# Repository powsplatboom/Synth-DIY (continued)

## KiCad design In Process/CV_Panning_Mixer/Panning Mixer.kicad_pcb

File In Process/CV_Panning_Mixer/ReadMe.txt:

Replacement design for the stereo mixer I built previously. 
Works relatively well, but panning circuit need reworked to achieve constant power panning. Distortion gain needs adjusted to achieve more constant volume.
Likely to switch to the SSI2164 with the redesign to save on cost and board size. The AS3360 is a finnicky chip that requires too many external components to function.
Will also be adding expandability to the board so that a microphone pre-amp can be added as a separate upgrade.
Would also like to add mute switches to all channels.

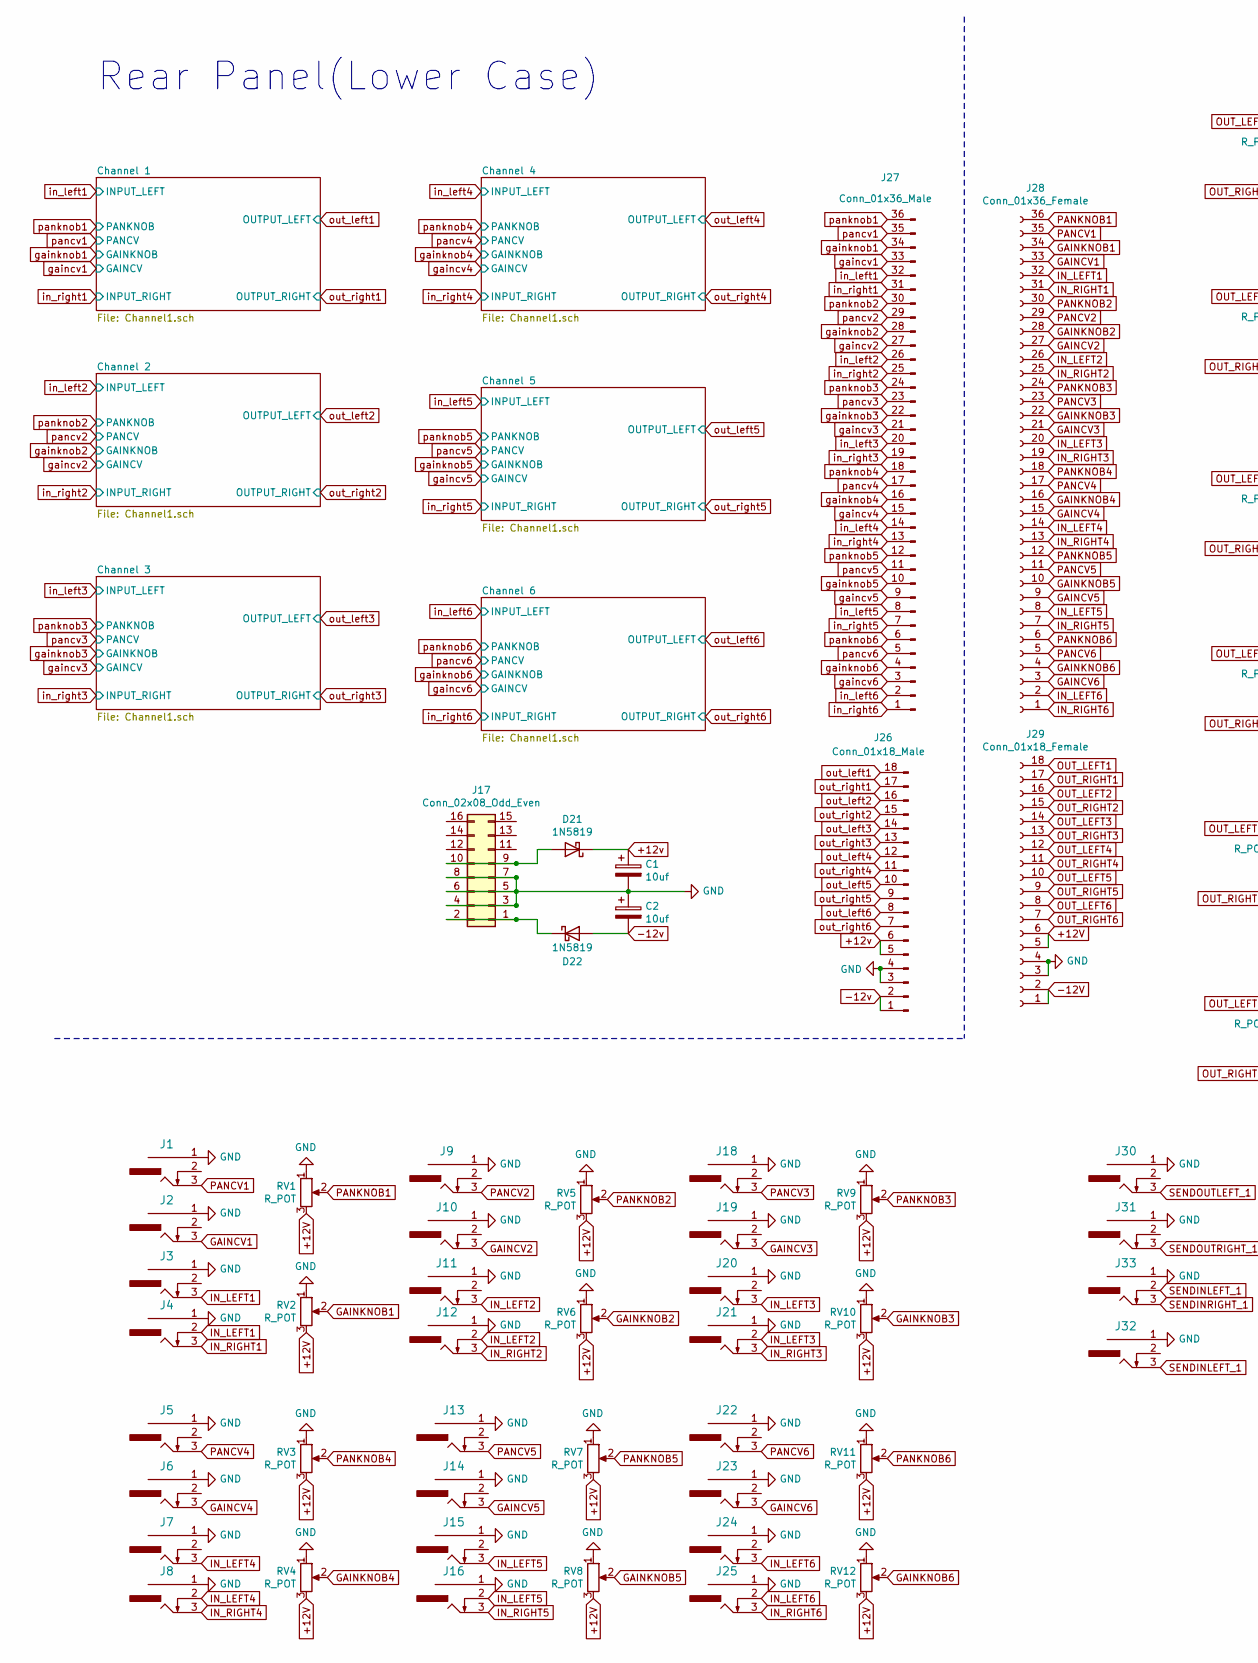
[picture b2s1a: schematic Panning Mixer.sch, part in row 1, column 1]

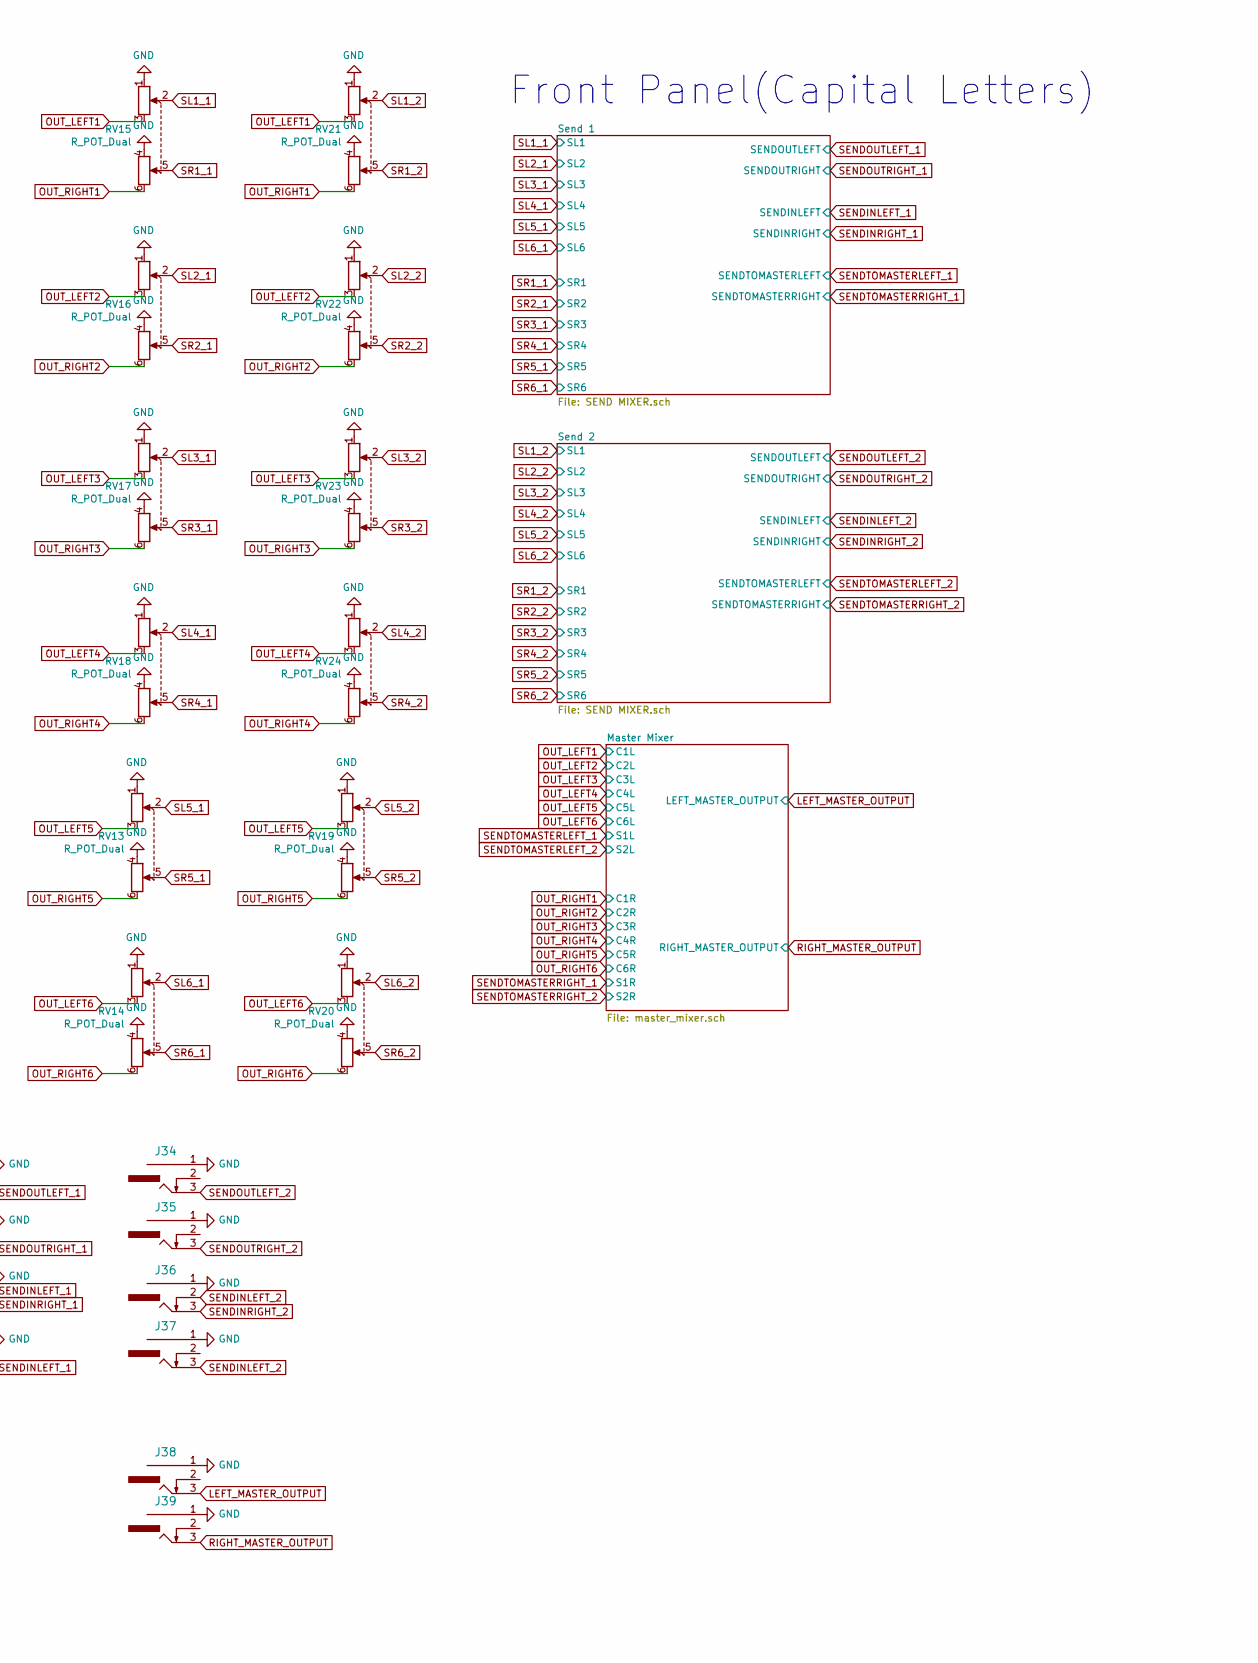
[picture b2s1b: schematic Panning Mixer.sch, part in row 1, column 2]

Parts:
C1, C2: 10uf; CP_Elec_5x5.4
D21, D22: 1N5819; D_DO-41_SOD81_P10.16mm_Horizontal
J1, J2, J3, J4, J5, J6, J7, J8, J9, J10, J11, J12, J13, J14, J15, J16, J18, J19, J20, J21, J22, J23, J24, J25, J30, J31, J32, J33, J34, J35, J36, J37, J38, J39: PJ301_THONKICONN1; PJ-3001_Mono_Phone
J17: Conn_02x08_Odd_Even; IDC-Header_2x08_P2.54mm_Vertical
J26: Conn_01x18_Male; PinHeader_1x18_P2.54mm_Vertical
J27: Conn_01x36_Male; PinHeader_1x36_P2.54mm_Vertical
J28: Conn_01x36_Female; PinSocket_1x36_P2.54mm_Vertical
J29: Conn_01x18_Female; PinSocket_1x18_P2.54mm_Vertical
RV1, RV2, RV3, RV4, RV5, RV6, RV7, RV8, RV9, RV10, RV11, RV12: R_POT; Potentiometer_Alpha_RD901F-40-00D_Single_Vertical
RV13, RV14, RV15, RV16, RV17, RV18, RV19, RV20, RV21, RV22, RV23, RV24: R_POT_Dual; Potentiometer_Alpha_RD902F-40-00D_Dual_Vertical

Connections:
+12V: J29.5, J29.6, RV1.3, RV2.3, RV3.3, RV4.3, RV5.3, RV6.3, RV7.3, RV8.3, RV9.3, RV10.3, RV11.3, RV12.3; also elsewhere on the board
+12v: C1.1, D21.1 (K), J26.5, J26.6; also elsewhere on the board
-12V: J29.1, J29.2; also elsewhere on the board
-12v: C2.2, D22.2 (A), J26.1, J26.2; also elsewhere on the board
GAINCV1: J2.3, J28.33
GAINCV2: J10.3, J28.27
GAINCV3: J19.3, J28.21
GAINCV4: J6.3, J28.15
GAINCV5: J14.3, J28.9
GAINCV6: J23.3, J28.3
GAINKNOB1: J28.34, RV2.2
GAINKNOB2: J28.28, RV6.2
GAINKNOB3: J28.22, RV10.2
GAINKNOB4: J28.16, RV4.2
GAINKNOB5: J28.10, RV8.2
GAINKNOB6: J28.4, RV12.2
GND: C1.2, C2.1, J1.1, J2.1, J3.1, J4.1, J5.1, J6.1, J7.1, J8.1, J9.1, J10.1, J11.1, J12.1, J13.1, J14.1, J15.1, J16.1, J17.3, J17.4, J17.5, J17.6, J17.7, J17.8, J18.1, J19.1, J20.1, J21.1, J22.1, J23.1, J24.1, J25.1, J26.3, J26.4, J29.3, J29.4, J30.1, J31.1, J32.1, J33.1, J34.1, J35.1, J36.1, J37.1, J38.1, J39.1, RV1.1, RV2.1, RV3.1, RV4.1, RV5.1, RV6.1, RV7.1, RV8.1, RV9.1, RV10.1, RV11.1, RV12.1, RV13.1, RV13.4, RV14.1, RV14.4, RV15.1, RV15.4, RV16.1, RV16.4, RV17.1, RV17.4, RV18.1, RV18.4, RV19.1, RV19.4, RV20.1, RV20.4, RV21.1, RV21.4, RV22.1, RV22.4, RV23.1, RV23.4, RV24.1, RV24.4; also elsewhere on the board
IN_LEFT1: J3.3, J4.2, J28.32
IN_LEFT2: J11.3, J12.2, J28.26
IN_LEFT3: J20.3, J21.2, J28.20
IN_LEFT4: J7.3, J8.2, J28.14
IN_LEFT5: J15.3, J16.2, J28.8
IN_LEFT6: J24.3, J25.2, J28.2
IN_RIGHT1: J4.3, J28.31
IN_RIGHT2: J12.3, J28.25
IN_RIGHT3: J21.3, J28.19
IN_RIGHT4: J8.3, J28.13
IN_RIGHT5: J16.3, J28.7
IN_RIGHT6: J25.3, J28.1
LEFT_MASTER_OUTPUT: J38.3; also elsewhere on the board
unnamed: D21.2 (A), J17.9, J17.10
unnamed: D22.1 (K), J17.1, J17.2
OUT_LEFT1: J29.18, RV15.3, RV21.3; also elsewhere on the board
OUT_LEFT2: J29.16, RV16.3, RV22.3; also elsewhere on the board
OUT_LEFT3: J29.14, RV17.3, RV23.3; also elsewhere on the board
OUT_LEFT4: J29.12, RV18.3, RV24.3; also elsewhere on the board
OUT_LEFT5: J29.10, RV13.3, RV19.3; also elsewhere on the board
OUT_LEFT6: J29.8, RV14.3, RV20.3; also elsewhere on the board
OUT_RIGHT1: J29.17, RV15.6, RV21.6; also elsewhere on the board
OUT_RIGHT2: J29.15, RV16.6, RV22.6; also elsewhere on the board
OUT_RIGHT3: J29.13, RV17.6, RV23.6; also elsewhere on the board
OUT_RIGHT4: J29.11, RV18.6, RV24.6; also elsewhere on the board
OUT_RIGHT5: J29.9, RV13.6, RV19.6; also elsewhere on the board
OUT_RIGHT6: J29.7, RV14.6, RV20.6; also elsewhere on the board
PANCV1: J1.3, J28.35
PANCV2: J9.3, J28.29
PANCV3: J18.3, J28.23
PANCV4: J5.3, J28.17
PANCV5: J13.3, J28.11
PANCV6: J22.3, J28.5
PANKNOB1: J28.36, RV1.2
PANKNOB2: J28.30, RV5.2
PANKNOB3: J28.24, RV9.2
PANKNOB4: J28.18, RV3.2
PANKNOB5: J28.12, RV7.2
PANKNOB6: J28.6, RV11.2
RIGHT_MASTER_OUTPUT: J39.3; also elsewhere on the board
SENDINRIGHT_1: J33.3; also elsewhere on the board
SENDINRIGHT_2: J36.3; also elsewhere on the board
SENDOUTLEFT_1: J30.3; also elsewhere on the board
SENDOUTLEFT_2: J34.3; also elsewhere on the board
SENDOUTRIGHT_1: J31.3; also elsewhere on the board
SENDOUTRIGHT_2: J35.3; also elsewhere on the board
SL1_1: RV15.2; also elsewhere on the board
SL1_2: RV21.2; also elsewhere on the board
SL2_1: RV16.2; also elsewhere on the board
SL2_2: RV22.2; also elsewhere on the board
SL3_1: RV17.2; also elsewhere on the board
SL3_2: RV23.2; also elsewhere on the board
SL4_1: RV18.2; also elsewhere on the board
SL4_2: RV24.2; also elsewhere on the board
SL5_1: RV13.2; also elsewhere on the board
SL5_2: RV19.2; also elsewhere on the board
SL6_1: RV14.2; also elsewhere on the board
SL6_2: RV20.2; also elsewhere on the board
SR1_1: RV15.5; also elsewhere on the board
SR1_2: RV21.5; also elsewhere on the board
SR2_1: RV16.5; also elsewhere on the board
SR2_2: RV22.5; also elsewhere on the board
SR3_1: RV17.5; also elsewhere on the board
SR3_2: RV23.5; also elsewhere on the board
SR4_1: RV18.5; also elsewhere on the board
SR4_2: RV24.5; also elsewhere on the board
SR5_1: RV13.5; also elsewhere on the board
SR5_2: RV19.5; also elsewhere on the board
SR6_1: RV14.5; also elsewhere on the board
SR6_2: RV20.5; also elsewhere on the board
gaincv1: J27.33; also elsewhere on the board
gaincv2: J27.27; also elsewhere on the board
gaincv3: J27.21; also elsewhere on the board
gaincv4: J27.15; also elsewhere on the board
gaincv5: J27.9; also elsewhere on the board
gaincv6: J27.3; also elsewhere on the board
gainknob1: J27.34; also elsewhere on the board
gainknob2: J27.28; also elsewhere on the board
gainknob3: J27.22; also elsewhere on the board
gainknob4: J27.16; also elsewhere on the board
gainknob5: J27.10; also elsewhere on the board
gainknob6: J27.4; also elsewhere on the board
in_left1: J27.32; also elsewhere on the board
in_left2: J27.26; also elsewhere on the board
in_left3: J27.20; also elsewhere on the board
in_left4: J27.14; also elsewhere on the board
in_left5: J27.8; also elsewhere on the board
in_left6: J27.2; also elsewhere on the board
in_right1: J27.31; also elsewhere on the board
in_right2: J27.25; also elsewhere on the board
in_right3: J27.19; also elsewhere on the board
in_right4: J27.13; also elsewhere on the board
in_right5: J27.7; also elsewhere on the board
in_right6: J27.1; also elsewhere on the board
out_left1: J26.18; also elsewhere on the board
out_left2: J26.16; also elsewhere on the board
out_left3: J26.14; also elsewhere on the board
out_left4: J26.12; also elsewhere on the board
out_left5: J26.10; also elsewhere on the board
out_left6: J26.8; also elsewhere on the board
out_right1: J26.17; also elsewhere on the board
out_right2: J26.15; also elsewhere on the board
out_right3: J26.13; also elsewhere on the board
out_right4: J26.11; also elsewhere on the board
out_right5: J26.9; also elsewhere on the board
out_right6: J26.7; also elsewhere on the board
pancv1: J27.35; also elsewhere on the board
pancv2: J27.29; also elsewhere on the board
pancv3: J27.23; also elsewhere on the board
pancv4: J27.17; also elsewhere on the board
pancv5: J27.11; also elsewhere on the board
pancv6: J27.5; also elsewhere on the board
panknob1: J27.36; also elsewhere on the board
panknob2: J27.30; also elsewhere on the board
panknob3: J27.24; also elsewhere on the board
panknob4: J27.18; also elsewhere on the board
panknob5: J27.12; also elsewhere on the board
panknob6: J27.6; also elsewhere on the board

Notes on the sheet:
Front Panel(Capital Letters)
Rear Panel(Lower Case)

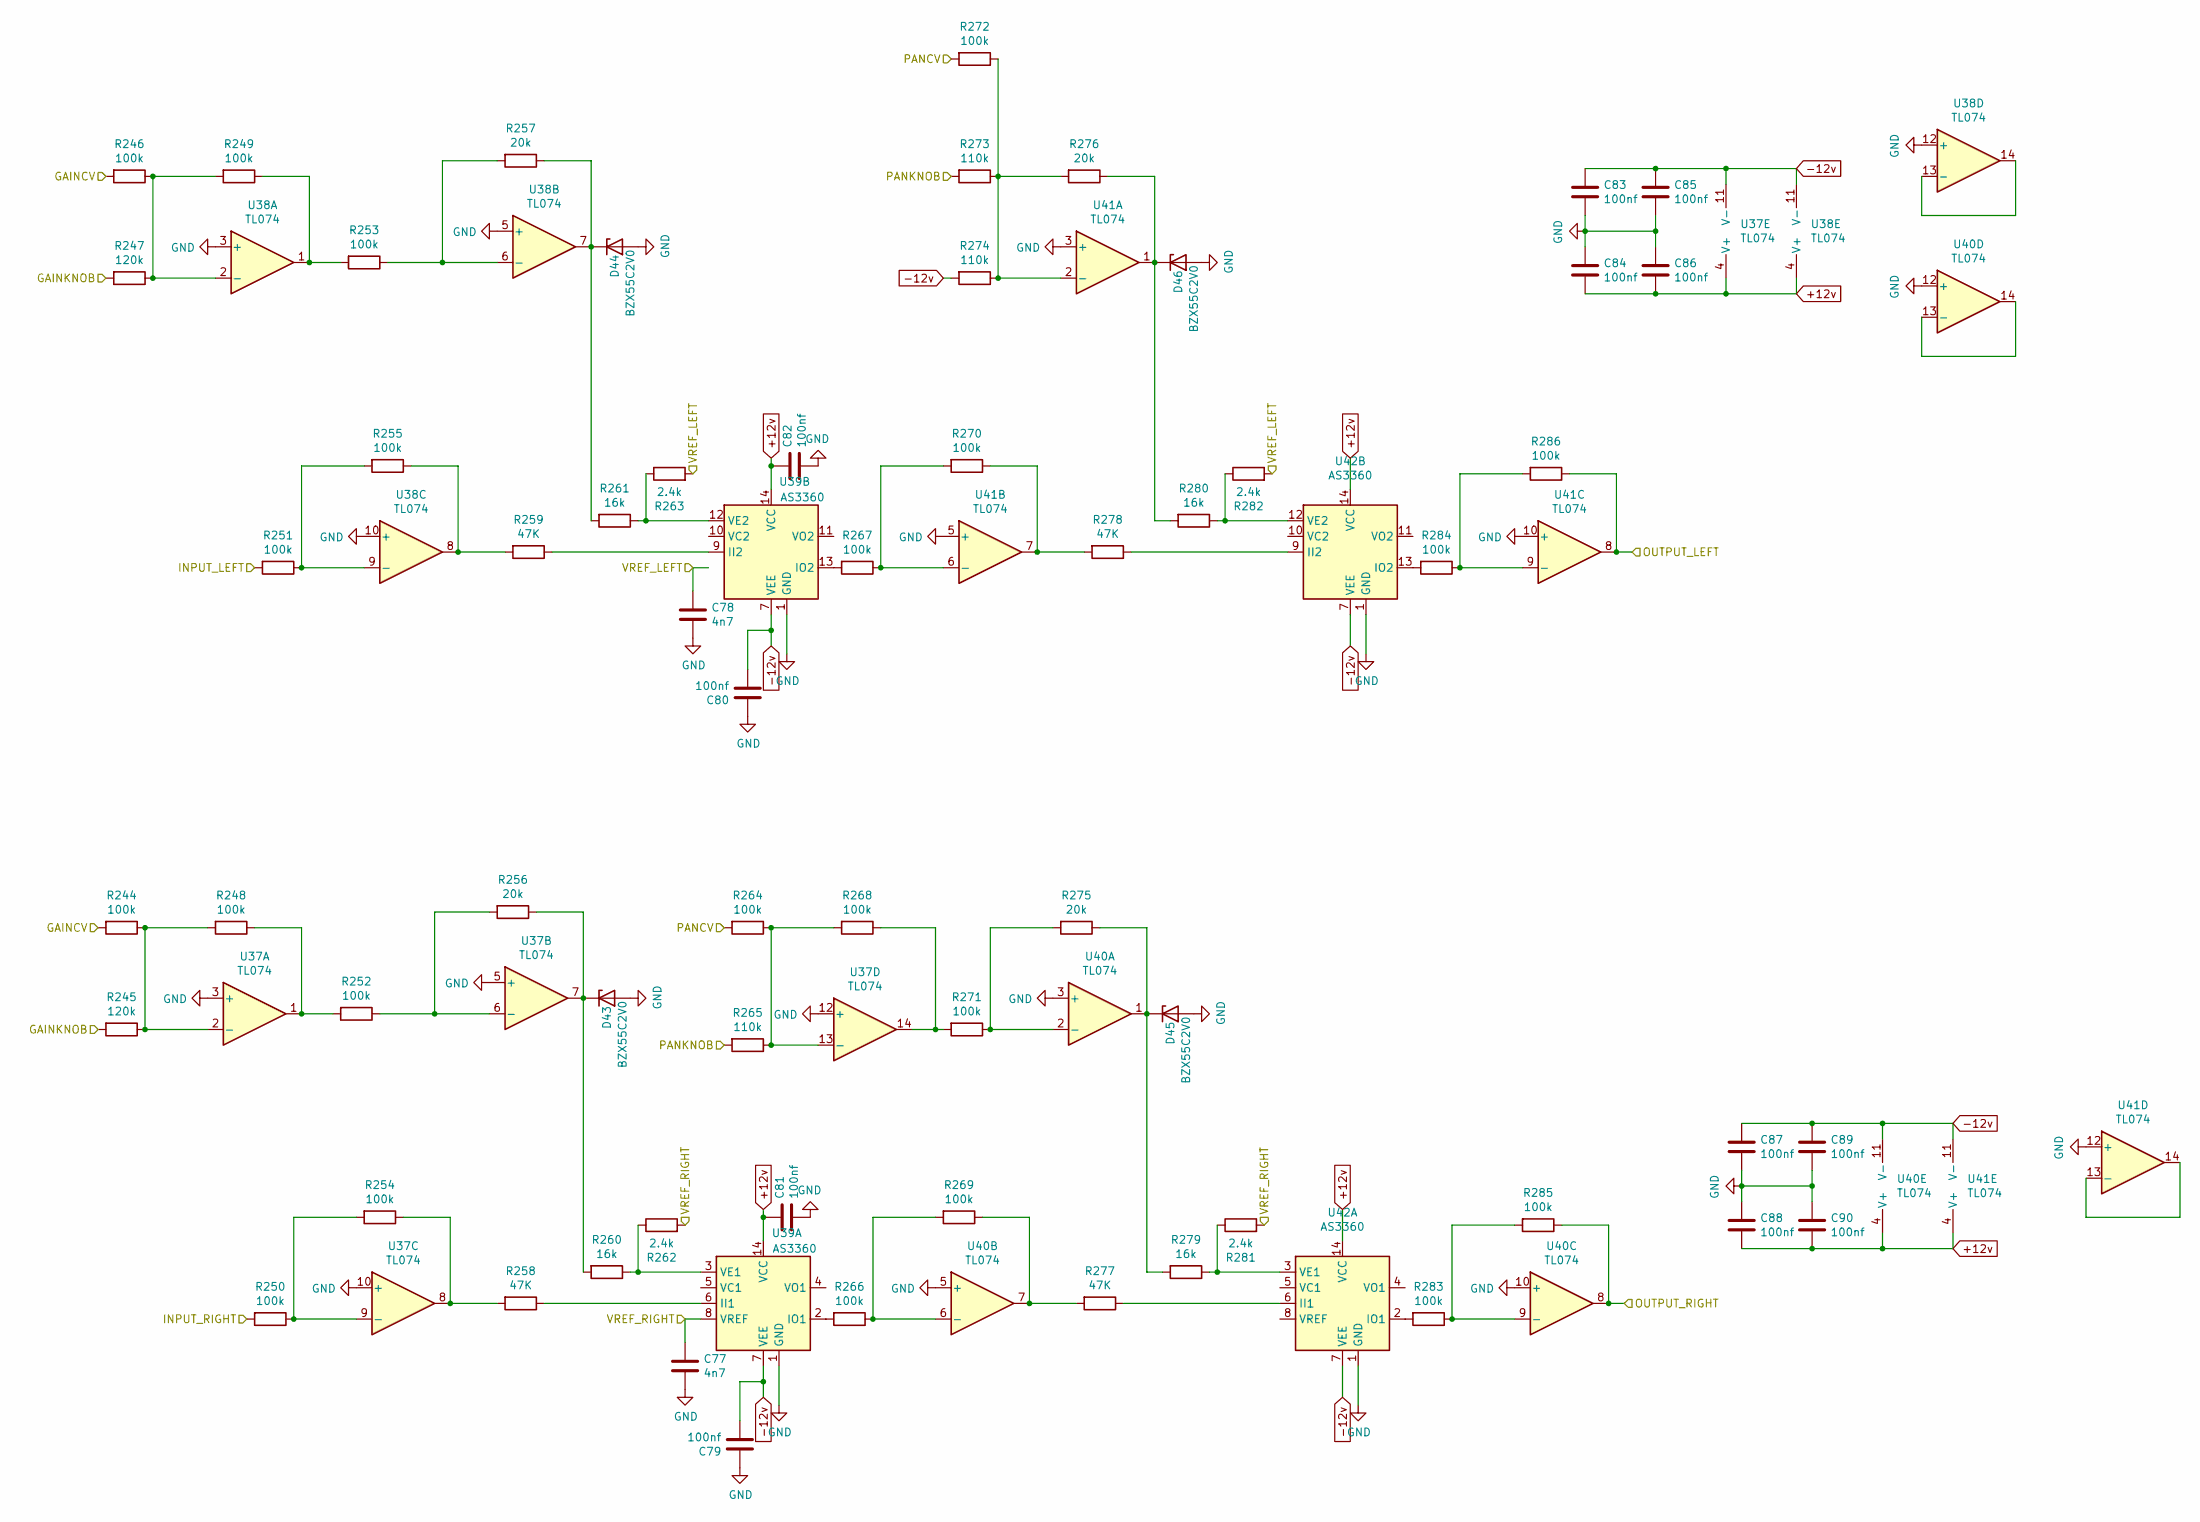
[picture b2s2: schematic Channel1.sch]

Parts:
C3, C4: 4n7; C_0603_1608Metric
C5, C6, C7, C8, C9, C10, C11, C14, C15, C18, C19, C20: 100nf; C_0603_1608Metric
D23, D24, D25, D26: BZX55C2V0; D_SOD-123
R1, R3, R5, R6, R7, R8, R9, R10, R11, R12, R21, R23, R24, R25, R26, R27, R28, R57, R68, R69, R70, R71: 100k; R_0603_1608Metric
R2, R4: 120k; R_0603_1608Metric
R13, R14, R60, R61: 20k; R_0603_1608Metric
R15, R16, R62, R63: 47K; R_0603_1608Metric
R17, R18, R64, R65: 16k; R_0603_1608Metric
R19, R20, R66, R67: 2.4k; R_0603_1608Metric
R22, R58, R59: 110k; R_0603_1608Metric
U7, U8, U10, U11: TL074; SOIC-14_3.9x8.7mm_P1.27mm
U9, U12: AS3360; DIP-14_W7.62mm_Socket

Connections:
+12v: C7.1, C8.1, C10.2, C14.2, C18.2, C20.2, U7.4 (V+), U8.4 (V+), U9.14 (VCC), U10.4 (V+), U11.4 (V+), U12.14 (VCC); also elsewhere on the board
-12v: C5.2, C6.2, C9.1, C11.1, C15.1, C19.1, R59.2, U7.11 (V-), U8.11 (V-), U9.7 (VEE), U10.11 (V-), U11.11 (V-), U12.7 (VEE); also elsewhere on the board
/Channel 1/VREF_LEFT: C4.1, R20.2, R67.2
/Channel 1/VREF_RIGHT: C3.1, R19.2, R66.2, U9.8 (VREF)
GND: C3.2, C4.2, C5.1, C6.1, C7.2, C8.2, C9.2, C10.1, C11.2, C14.1, C15.2, C18.1, C19.2, C20.1, D23.2 (A), D24.2 (A), D25.2 (A), D26.2 (A), U7.3 (+), U7.5 (+), U7.10 (+), U7.12 (+), U8.3 (+), U8.5 (+), U8.10 (+), U8.12 (+), U9.1 (GND), U10.3 (+), U10.5 (+), U10.10 (+), U10.12 (+), U11.3 (+), U11.5 (+), U11.10 (+), U11.12 (+), U12.1 (GND); also elsewhere on the board
unnamed: D23.1 (K), R13.1, R17.2, U7.7
unnamed: D24.1 (K), R14.1, R18.2, U8.7
unnamed: D25.1 (K), R60.1, R64.2, U10.1
unnamed: D26.1 (K), R61.1, R65.2, U11.1
unnamed: R1.1, R2.1, R5.2, U7.2 (-)
unnamed: R3.1, R4.1, R6.2, U8.2 (-)
unnamed: R5.1, R9.2, U7.1
unnamed: R10.1, R14.2, U8.6 (-)
unnamed: R6.1, R10.2, U8.1
unnamed: R11.1, R15.2, U7.8
unnamed: R7.1, R11.2, U7.9 (-)
unnamed: R12.1, R16.2, U8.8
unnamed: R8.1, R12.2, U8.9 (-)
unnamed: R9.1, R13.2, U7.6 (-)
unnamed: R15.1, U9.6 (II1)
unnamed: R16.1, U9.9 (II2)
unnamed: R17.1, R19.1, U9.3 (VE1)
unnamed: R18.1, R20.1, U9.12 (VE2)
unnamed: R21.1, R22.1, R25.2, U7.13 (-)
unnamed: R23.1, R26.2, U10.6 (-)
unnamed: R23.2, U9.2 (IO1)
unnamed: R24.1, R27.2, U11.6 (-)
unnamed: R24.2, U9.13 (IO2)
unnamed: R25.1, R28.2, U7.14
unnamed: R26.1, R62.2, U10.7
unnamed: R27.1, R63.2, U11.7
unnamed: R28.1, R60.2, U10.2 (-)
unnamed: R57.1, R58.1, R59.1, R61.2, U11.2 (-)
unnamed: R62.1, U12.6 (II1)
unnamed: R63.1, U12.9 (II2)
unnamed: R64.1, R66.1, U12.3 (VE1)
unnamed: R65.1, R67.1, U12.12 (VE2)
unnamed: R68.1, R70.2, U10.9 (-)
unnamed: R68.2, U12.2 (IO1)
unnamed: R69.1, R71.2, U11.9 (-)
unnamed: R69.2, U12.13 (IO2)
unnamed: U8.13 (-), U8.14
unnamed: U10.13 (-), U10.14
unnamed: U11.13 (-), U11.14
gaincv1: R1.2, R3.2; also elsewhere on the board
gainknob1: R2.2, R4.2; also elsewhere on the board
in_left1: R8.2; also elsewhere on the board
in_right1: R7.2; also elsewhere on the board
out_left1: R71.1, U11.8; also elsewhere on the board
out_right1: R70.1, U10.8; also elsewhere on the board
pancv1: R21.2, R57.2; also elsewhere on the board
panknob1: R22.2, R58.2; also elsewhere on the board

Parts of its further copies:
C21, C22, C35, C36, C49, C50, C63, C64, C77, C78: 4n7; C_0603_1608Metric
C23, C24, C25, C26, C27, C28, C29, C30, C31, C32, C33, C34, C37, C38, C39, C40, C41, C42, C43, C44, C45, C46, C47, C48, C51, C52, C53, C54, C55, C56, C57, C58, C59, C60, C61, C62, C65, C66, C67, C68, C69, C70, C71, C72, C73, C74, C75, C76, C79, C80, C81, C82, C83, C84, C85, C86, C87, C88, C89, C90: 100nf; C_0603_1608Metric
D27, D28, D29, D30, D31, D32, D33, D34, D35, D36, D37, D38, D39, D40, D41, D42, D43, D44, D45, D46: BZX55C2V0; D_SOD-123
R72, R74, R76, R77, R78, R79, R80, R81, R82, R83, R92, R94, R95, R96, R97, R98, R99, R100, R111, R112, R113, R114, R115, R117, R119, R120, R121, R122, R123, R124, R125, R126, R135, R137, R138, R139, R140, R141, R142, R143, R154, R155, R156, R157, R158, R160, R162, R163, R164, R165, R166, R167, R168, R169, R178, R180, R181, R182, R183, R184, R185, R186, R197, R198, R199, R200, R201, R203, R205, R206, R207, R208, R209, R210, R211, R212, R221, R223, R224, R225, R226, R227, R228, R229, R240, R241, R242, R243, R244, R246, R248, R249, R250, R251, R252, R253, R254, R255, R264, R266, R267, R268, R269, R270, R271, R272, R283, R284, R285, R286: 100k; R_0603_1608Metric
R73, R75, R116, R118, R159, R161, R202, R204, R245, R247: 120k; R_0603_1608Metric
R84, R85, R103, R104, R127, R128, R146, R147, R170, R171, R189, R190, R213, R214, R232, R233, R256, R257, R275, R276: 20k; R_0603_1608Metric
R86, R87, R105, R106, R129, R130, R148, R149, R172, R173, R191, R192, R215, R216, R234, R235, R258, R259, R277, R278: 47K; R_0603_1608Metric
R88, R89, R107, R108, R131, R132, R150, R151, R174, R175, R193, R194, R217, R218, R236, R237, R260, R261, R279, R280: 16k; R_0603_1608Metric
R90, R91, R109, R110, R133, R134, R152, R153, R176, R177, R195, R196, R219, R220, R238, R239, R262, R263, R281, R282: 2.4k; R_0603_1608Metric
R93, R101, R102, R136, R144, R145, R179, R187, R188, R222, R230, R231, R265, R273, R274: 110k; R_0603_1608Metric
U13, U14, U16, U17, U19, U20, U22, U23, U25, U26, U28, U29, U31, U32, U34, U35, U37, U38, U40, U41: TL074; SOIC-14_3.9x8.7mm_P1.27mm
U15, U18, U21, U24, U27, U30, U33, U36, U39, U42: AS3360; DIP-14_W7.62mm_Socket

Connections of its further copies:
+12v: C25.1, C26.1, C28.2, C30.2, C32.2, C34.2, C39.1, C40.1, C42.2, C44.2, C46.2, C48.2, C53.1, C54.1, C56.2, C58.2, C60.2, C62.2, C67.1, C68.1, C70.2, C72.2, C74.2, C76.2, C81.1, C82.1, C84.2, C86.2, C88.2, C90.2, U13.4 (V+), U14.4 (V+), U15.14 (VCC), U16.4 (V+), U17.4 (V+), U18.14 (VCC), U19.4 (V+), U20.4 (V+), U21.14 (VCC), U22.4 (V+), U23.4 (V+), U24.14 (VCC), U25.4 (V+), U26.4 (V+), U27.14 (VCC), U28.4 (V+), U29.4 (V+), U30.14 (VCC), U31.4 (V+), U32.4 (V+), U33.14 (VCC), U34.4 (V+), U35.4 (V+), U36.14 (VCC), U37.4 (V+), U38.4 (V+), U39.14 (VCC), U40.4 (V+), U41.4 (V+), U42.14 (VCC); also elsewhere on the board
-12v: C23.2, C24.2, C27.1, C29.1, C31.1, C33.1, C37.2, C38.2, C41.1, C43.1, C45.1, C47.1, C51.2, C52.2, C55.1, C57.1, C59.1, C61.1, C65.2, C66.2, C69.1, C71.1, C73.1, C75.1, C79.2, C80.2, C83.1, C85.1, C87.1, C89.1, R102.2, R145.2, R188.2, R231.2, R274.2, U13.11 (V-), U14.11 (V-), U15.7 (VEE), U16.11 (V-), U17.11 (V-), U18.7 (VEE), U19.11 (V-), U20.11 (V-), U21.7 (VEE), U22.11 (V-), U23.11 (V-), U24.7 (VEE), U25.11 (V-), U26.11 (V-), U27.7 (VEE), U28.11 (V-), U29.11 (V-), U30.7 (VEE), U31.11 (V-), U32.11 (V-), U33.7 (VEE), U34.11 (V-), U35.11 (V-), U36.7 (VEE), U37.11 (V-), U38.11 (V-), U39.7 (VEE), U40.11 (V-), U41.11 (V-), U42.7 (VEE); also elsewhere on the board
/Channel 2/VREF_LEFT: C22.1, R91.2, R110.2
/Channel 2/VREF_RIGHT: C21.1, R90.2, R109.2, U15.8 (VREF)
/Channel 3/VREF_LEFT: C36.1, R134.2, R153.2
/Channel 3/VREF_RIGHT: C35.1, R133.2, R152.2, U21.8 (VREF)
/Channel 4/VREF_LEFT: C50.1, R177.2, R196.2
/Channel 4/VREF_RIGHT: C49.1, R176.2, R195.2, U27.8 (VREF)
/Channel 5/VREF_LEFT: C64.1, R220.2, R239.2
/Channel 5/VREF_RIGHT: C63.1, R219.2, R238.2, U33.8 (VREF)
/Channel 6/VREF_LEFT: C78.1, R263.2, R282.2
/Channel 6/VREF_RIGHT: C77.1, R262.2, R281.2, U39.8 (VREF)
GND: C21.2, C22.2, C23.1, C24.1, C25.2, C26.2, C27.2, C28.1, C29.2, C30.1, C31.2, C32.1, C33.2, C34.1, C35.2, C36.2, C37.1, C38.1, C39.2, C40.2, C41.2, C42.1, C43.2, C44.1, C45.2, C46.1, C47.2, C48.1, C49.2, C50.2, C51.1, C52.1, C53.2, C54.2, C55.2, C56.1, C57.2, C58.1, C59.2, C60.1, C61.2, C62.1, C63.2, C64.2, C65.1, C66.1, C67.2, C68.2, C69.2, C70.1, C71.2, C72.1, C73.2, C74.1, C75.2, C76.1, C77.2, C78.2, C79.1, C80.1, C81.2, C82.2, C83.2, C84.1, C85.2, C86.1, C87.2, C88.1, C89.2, C90.1, D27.2 (A), D28.2 (A), D29.2 (A), D30.2 (A), D31.2 (A), D32.2 (A), D33.2 (A), D34.2 (A), D35.2 (A), D36.2 (A), D37.2 (A), D38.2 (A), D39.2 (A), D40.2 (A), D41.2 (A), D42.2 (A), D43.2 (A), D44.2 (A), D45.2 (A), D46.2 (A), U13.3 (+), U13.5 (+), U13.10 (+), U13.12 (+), U14.3 (+), U14.5 (+), U14.10 (+), U14.12 (+), U15.1 (GND), U16.3 (+), U16.5 (+), U16.10 (+), U16.12 (+), U17.3 (+), U17.5 (+), U17.10 (+), U17.12 (+), U18.1 (GND), U19.3 (+), U19.5 (+), U19.10 (+), U19.12 (+), U20.3 (+), U20.5 (+), U20.10 (+), U20.12 (+), U21.1 (GND), U22.3 (+), U22.5 (+), U22.10 (+), U22.12 (+), U23.3 (+), U23.5 (+), U23.10 (+), U23.12 (+), U24.1 (GND), U25.3 (+), U25.5 (+), U25.10 (+), U25.12 (+), U26.3 (+), U26.5 (+), U26.10 (+), U26.12 (+), U27.1 (GND), U28.3 (+), U28.5 (+), U28.10 (+), U28.12 (+), U29.3 (+), U29.5 (+), U29.10 (+), U29.12 (+), U30.1 (GND), U31.3 (+), U31.5 (+), U31.10 (+), U31.12 (+), U32.3 (+), U32.5 (+), U32.10 (+), U32.12 (+), U33.1 (GND), U34.3 (+), U34.5 (+), U34.10 (+), U34.12 (+), U35.3 (+), U35.5 (+), U35.10 (+), U35.12 (+), U36.1 (GND), U37.3 (+), U37.5 (+), U37.10 (+), U37.12 (+), U38.3 (+), U38.5 (+), U38.10 (+), U38.12 (+), U39.1 (GND), U40.3 (+), U40.5 (+), U40.10 (+), U40.12 (+), U41.3 (+), U41.5 (+), U41.10 (+), U41.12 (+), U42.1 (GND); also elsewhere on the board
unnamed: D27.1 (K), R84.1, R88.2, U13.7
unnamed: D28.1 (K), R85.1, R89.2, U14.7
unnamed: D29.1 (K), R103.1, R107.2, U16.1
unnamed: D30.1 (K), R104.1, R108.2, U17.1
unnamed: D31.1 (K), R127.1, R131.2, U19.7
unnamed: D32.1 (K), R128.1, R132.2, U20.7
unnamed: D33.1 (K), R146.1, R150.2, U22.1
unnamed: D34.1 (K), R147.1, R151.2, U23.1
unnamed: D35.1 (K), R170.1, R174.2, U25.7
unnamed: D36.1 (K), R171.1, R175.2, U26.7
unnamed: D37.1 (K), R189.1, R193.2, U28.1
unnamed: D38.1 (K), R190.1, R194.2, U29.1
unnamed: D39.1 (K), R213.1, R217.2, U31.7
unnamed: D40.1 (K), R214.1, R218.2, U32.7
unnamed: D41.1 (K), R232.1, R236.2, U34.1
unnamed: D42.1 (K), R233.1, R237.2, U35.1
unnamed: D43.1 (K), R256.1, R260.2, U37.7
unnamed: D44.1 (K), R257.1, R261.2, U38.7
unnamed: D45.1 (K), R275.1, R279.2, U40.1
unnamed: D46.1 (K), R276.1, R280.2, U41.1
unnamed: R72.1, R73.1, R76.2, U13.2 (-)
unnamed: R74.1, R75.1, R77.2, U14.2 (-)
unnamed: R76.1, R80.2, U13.1
unnamed: R77.1, R81.2, U14.1
unnamed: R78.1, R82.2, U13.9 (-)
unnamed: R79.1, R83.2, U14.9 (-)
unnamed: R80.1, R84.2, U13.6 (-)
unnamed: R81.1, R85.2, U14.6 (-)
unnamed: R82.1, R86.2, U13.8
unnamed: R83.1, R87.2, U14.8
unnamed: R86.1, U15.6 (II1)
unnamed: R87.1, U15.9 (II2)
unnamed: R88.1, R90.1, U15.3 (VE1)
unnamed: R89.1, R91.1, U15.12 (VE2)
unnamed: R92.1, R93.1, R96.2, U13.13 (-)
unnamed: R94.1, R97.2, U16.6 (-)
unnamed: R94.2, U15.2 (IO1)
unnamed: R95.1, R98.2, U17.6 (-)
unnamed: R95.2, U15.13 (IO2)
unnamed: R96.1, R99.2, U13.14
unnamed: R100.1, R101.1, R102.1, R104.2, U17.2 (-)
unnamed: R99.1, R103.2, U16.2 (-)
unnamed: R105.1, U18.6 (II1)
unnamed: R97.1, R105.2, U16.7
unnamed: R106.1, U18.9 (II2)
unnamed: R98.1, R106.2, U17.7
unnamed: R107.1, R109.1, U18.3 (VE1)
unnamed: R108.1, R110.1, U18.12 (VE2)
unnamed: R111.1, R113.2, U16.9 (-)
unnamed: R111.2, U18.2 (IO1)
unnamed: R112.1, R114.2, U17.9 (-)
unnamed: R112.2, U18.13 (IO2)
unnamed: R115.1, R116.1, R119.2, U19.2 (-)
unnamed: R117.1, R118.1, R120.2, U20.2 (-)
unnamed: R119.1, R123.2, U19.1
unnamed: R120.1, R124.2, U20.1
unnamed: R121.1, R125.2, U19.9 (-)
unnamed: R122.1, R126.2, U20.9 (-)
unnamed: R123.1, R127.2, U19.6 (-)
unnamed: R124.1, R128.2, U20.6 (-)
unnamed: R125.1, R129.2, U19.8
unnamed: R126.1, R130.2, U20.8
unnamed: R129.1, U21.6 (II1)
unnamed: R130.1, U21.9 (II2)
unnamed: R131.1, R133.1, U21.3 (VE1)
unnamed: R132.1, R134.1, U21.12 (VE2)
unnamed: R135.1, R136.1, R139.2, U19.13 (-)
unnamed: R137.1, R140.2, U22.6 (-)
unnamed: R137.2, U21.2 (IO1)
unnamed: R138.1, R141.2, U23.6 (-)
unnamed: R138.2, U21.13 (IO2)
unnamed: R139.1, R142.2, U19.14
unnamed: R140.1, R148.2, U22.7
unnamed: R141.1, R149.2, U23.7
unnamed: R142.1, R146.2, U22.2 (-)
unnamed: R143.1, R144.1, R145.1, R147.2, U23.2 (-)
unnamed: R148.1, U24.6 (II1)
unnamed: R149.1, U24.9 (II2)
unnamed: R150.1, R152.1, U24.3 (VE1)
unnamed: R151.1, R153.1, U24.12 (VE2)
unnamed: R154.1, R156.2, U22.9 (-)
unnamed: R154.2, U24.2 (IO1)
unnamed: R155.1, R157.2, U23.9 (-)
unnamed: R155.2, U24.13 (IO2)
unnamed: R158.1, R159.1, R162.2, U25.2 (-)
unnamed: R160.1, R161.1, R163.2, U26.2 (-)
unnamed: R162.1, R166.2, U25.1
unnamed: R163.1, R167.2, U26.1
unnamed: R164.1, R168.2, U25.9 (-)
unnamed: R165.1, R169.2, U26.9 (-)
unnamed: R166.1, R170.2, U25.6 (-)
unnamed: R167.1, R171.2, U26.6 (-)
unnamed: R168.1, R172.2, U25.8
unnamed: R169.1, R173.2, U26.8
unnamed: R172.1, U27.6 (II1)
unnamed: R173.1, U27.9 (II2)
unnamed: R174.1, R176.1, U27.3 (VE1)
unnamed: R175.1, R177.1, U27.12 (VE2)
unnamed: R178.1, R179.1, R182.2, U25.13 (-)
unnamed: R180.1, R183.2, U28.6 (-)
unnamed: R180.2, U27.2 (IO1)
unnamed: R181.1, R184.2, U29.6 (-)
unnamed: R181.2, U27.13 (IO2)
unnamed: R182.1, R185.2, U25.14
unnamed: R183.1, R191.2, U28.7
unnamed: R184.1, R192.2, U29.7
unnamed: R185.1, R189.2, U28.2 (-)
unnamed: R186.1, R187.1, R188.1, R190.2, U29.2 (-)
unnamed: R191.1, U30.6 (II1)
unnamed: R192.1, U30.9 (II2)
unnamed: R193.1, R195.1, U30.3 (VE1)
unnamed: R194.1, R196.1, U30.12 (VE2)
unnamed: R197.1, R199.2, U28.9 (-)
unnamed: R197.2, U30.2 (IO1)
unnamed: R198.1, R200.2, U29.9 (-)
unnamed: R198.2, U30.13 (IO2)
unnamed: R201.1, R202.1, R205.2, U31.2 (-)
unnamed: R203.1, R204.1, R206.2, U32.2 (-)
unnamed: R205.1, R209.2, U31.1
unnamed: R206.1, R210.2, U32.1
unnamed: R207.1, R211.2, U31.9 (-)
unnamed: R208.1, R212.2, U32.9 (-)
unnamed: R209.1, R213.2, U31.6 (-)
unnamed: R210.1, R214.2, U32.6 (-)
unnamed: R211.1, R215.2, U31.8
unnamed: R212.1, R216.2, U32.8
unnamed: R215.1, U33.6 (II1)
unnamed: R216.1, U33.9 (II2)
unnamed: R217.1, R219.1, U33.3 (VE1)
unnamed: R218.1, R220.1, U33.12 (VE2)
unnamed: R221.1, R222.1, R225.2, U31.13 (-)
unnamed: R223.1, R226.2, U34.6 (-)
unnamed: R223.2, U33.2 (IO1)
unnamed: R224.1, R227.2, U35.6 (-)
unnamed: R224.2, U33.13 (IO2)
unnamed: R225.1, R228.2, U31.14
unnamed: R226.1, R234.2, U34.7
unnamed: R227.1, R235.2, U35.7
unnamed: R228.1, R232.2, U34.2 (-)
unnamed: R229.1, R230.1, R231.1, R233.2, U35.2 (-)
unnamed: R234.1, U36.6 (II1)
unnamed: R235.1, U36.9 (II2)
unnamed: R236.1, R238.1, U36.3 (VE1)
unnamed: R237.1, R239.1, U36.12 (VE2)
unnamed: R240.1, R242.2, U34.9 (-)
unnamed: R240.2, U36.2 (IO1)
unnamed: R241.1, R243.2, U35.9 (-)
unnamed: R241.2, U36.13 (IO2)
unnamed: R244.1, R245.1, R248.2, U37.2 (-)
unnamed: R246.1, R247.1, R249.2, U38.2 (-)
unnamed: R248.1, R252.2, U37.1
unnamed: R249.1, R253.2, U38.1
unnamed: R250.1, R254.2, U37.9 (-)
unnamed: R251.1, R255.2, U38.9 (-)
unnamed: R252.1, R256.2, U37.6 (-)
unnamed: R253.1, R257.2, U38.6 (-)
unnamed: R254.1, R258.2, U37.8
unnamed: R255.1, R259.2, U38.8
unnamed: R258.1, U39.6 (II1)
unnamed: R259.1, U39.9 (II2)
unnamed: R260.1, R262.1, U39.3 (VE1)
unnamed: R261.1, R263.1, U39.12 (VE2)
unnamed: R264.1, R265.1, R268.2, U37.13 (-)
unnamed: R266.1, R269.2, U40.6 (-)
unnamed: R266.2, U39.2 (IO1)
unnamed: R267.1, R270.2, U41.6 (-)
unnamed: R267.2, U39.13 (IO2)
unnamed: R268.1, R271.2, U37.14
unnamed: R269.1, R277.2, U40.7
unnamed: R270.1, R278.2, U41.7
unnamed: R271.1, R275.2, U40.2 (-)
unnamed: R272.1, R273.1, R274.1, R276.2, U41.2 (-)
unnamed: R277.1, U42.6 (II1)
unnamed: R278.1, U42.9 (II2)
unnamed: R279.1, R281.1, U42.3 (VE1)
unnamed: R280.1, R282.1, U42.12 (VE2)
unnamed: R283.1, R285.2, U40.9 (-)
unnamed: R283.2, U42.2 (IO1)
unnamed: R284.1, R286.2, U41.9 (-)
unnamed: R284.2, U42.13 (IO2)
unnamed: U14.13 (-), U14.14
unnamed: U16.13 (-), U16.14
unnamed: U17.13 (-), U17.14
unnamed: U20.13 (-), U20.14
unnamed: U22.13 (-), U22.14
unnamed: U23.13 (-), U23.14
unnamed: U26.13 (-), U26.14
unnamed: U28.13 (-), U28.14
unnamed: U29.13 (-), U29.14
unnamed: U32.13 (-), U32.14
unnamed: U34.13 (-), U34.14
unnamed: U35.13 (-), U35.14
unnamed: U38.13 (-), U38.14
unnamed: U40.13 (-), U40.14
unnamed: U41.13 (-), U41.14
gaincv2: R72.2, R74.2; also elsewhere on the board
gaincv3: R115.2, R117.2; also elsewhere on the board
gaincv4: R158.2, R160.2; also elsewhere on the board
gaincv5: R201.2, R203.2; also elsewhere on the board
gaincv6: R244.2, R246.2; also elsewhere on the board
gainknob2: R73.2, R75.2; also elsewhere on the board
gainknob3: R116.2, R118.2; also elsewhere on the board
gainknob4: R159.2, R161.2; also elsewhere on the board
gainknob5: R202.2, R204.2; also elsewhere on the board
gainknob6: R245.2, R247.2; also elsewhere on the board
in_left2: R79.2; also elsewhere on the board
in_left3: R122.2; also elsewhere on the board
in_left4: R165.2; also elsewhere on the board
in_left5: R208.2; also elsewhere on the board
in_left6: R251.2; also elsewhere on the board
in_right2: R78.2; also elsewhere on the board
in_right3: R121.2; also elsewhere on the board
in_right4: R164.2; also elsewhere on the board
in_right5: R207.2; also elsewhere on the board
in_right6: R250.2; also elsewhere on the board
out_left2: R114.1, U17.8; also elsewhere on the board
out_left3: R157.1, U23.8; also elsewhere on the board
out_left4: R200.1, U29.8; also elsewhere on the board
out_left5: R243.1, U35.8; also elsewhere on the board
out_left6: R286.1, U41.8; also elsewhere on the board
out_right2: R113.1, U16.8; also elsewhere on the board
out_right3: R156.1, U22.8; also elsewhere on the board
out_right4: R199.1, U28.8; also elsewhere on the board
out_right5: R242.1, U34.8; also elsewhere on the board
out_right6: R285.1, U40.8; also elsewhere on the board
pancv2: R92.2, R100.2; also elsewhere on the board
pancv3: R135.2, R143.2; also elsewhere on the board
pancv4: R178.2, R186.2; also elsewhere on the board
pancv5: R221.2, R229.2; also elsewhere on the board
pancv6: R264.2, R272.2; also elsewhere on the board
panknob2: R93.2, R101.2; also elsewhere on the board
panknob3: R136.2, R144.2; also elsewhere on the board
panknob4: R179.2, R187.2; also elsewhere on the board
panknob5: R222.2, R230.2; also elsewhere on the board
panknob6: R265.2, R273.2; also elsewhere on the board
